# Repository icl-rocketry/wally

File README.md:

# Sirius

Sirius is a two stage rocket being designed and built by ICLR's Altitude Record Team (ART). This repository contains the avionics hardware and software for the rocket.

Sirius has multiple avionics systems on board, with a combination of COTS and SRAD boards used for maximum redundancy and functionality. 

COTS components used:
* [Featherweight Blue Raven](https://www.featherweightaltimeters.com/blue-raven-altimeter.html) flight computer (x2)
* [Featherweight GPS Tracker](https://www.featherweightaltimeters.com/featherweight-gps-tracker.html) (sustainer only)
* [Vodafone Curve](https://eshop.v.vodafone.com/uk/curve-gps-tracker) (booster only)

SRAD boards used:
* Pickle [(developed here)](https://github.com/icl-rocketry/Ricardo-PickleRick)
* WALLY
* Lockie
* PDU

This repository is used for the development of WALLY, Lockie, the PDU and various helper boards. 

## WALLY: Wide Area Landing Location sYstem

Wally complements the COTS trackers and the GPS system onboard Pickle to provide an independent method for trajectory reconstruction and telemetry.

It contains the following elements:
* Microcontroller - ESP32-S3
* GPS - SIM7600G
* LTE - SIM7600G
* RTC - DS3231
* 868MHz LoRa - SX1262
* Barometer - DSP368
* IMU
* Magnetometer
* Storage - Micro SD

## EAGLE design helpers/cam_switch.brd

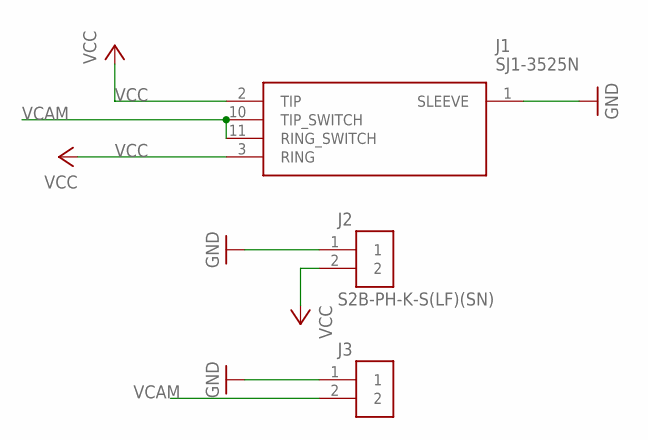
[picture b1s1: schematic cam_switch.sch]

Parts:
J1: SJ1-3525N; SJ13525N
J2, J3: S2B-PH-K-S(LF)(SN)

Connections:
GND: J1.1 (SLEEVE), J2.1, J3.1
VCAM: J1.10 (TIP_SWITCH), J1.11 (RING_SWITCH), J3.2
VCC: J1.2 (TIP), J1.3 (RING), J2.2

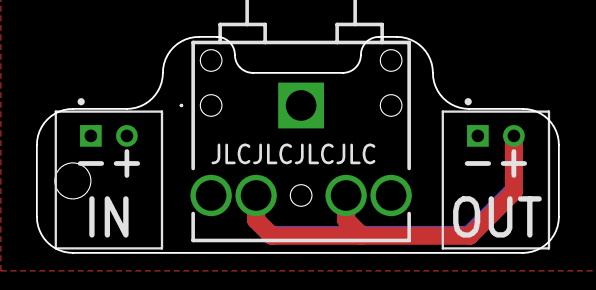
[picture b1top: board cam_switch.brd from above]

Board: 2 copper layers, 29.0 x 12.0 mm, 3 parts (0 on the bottom side), 3 nets.

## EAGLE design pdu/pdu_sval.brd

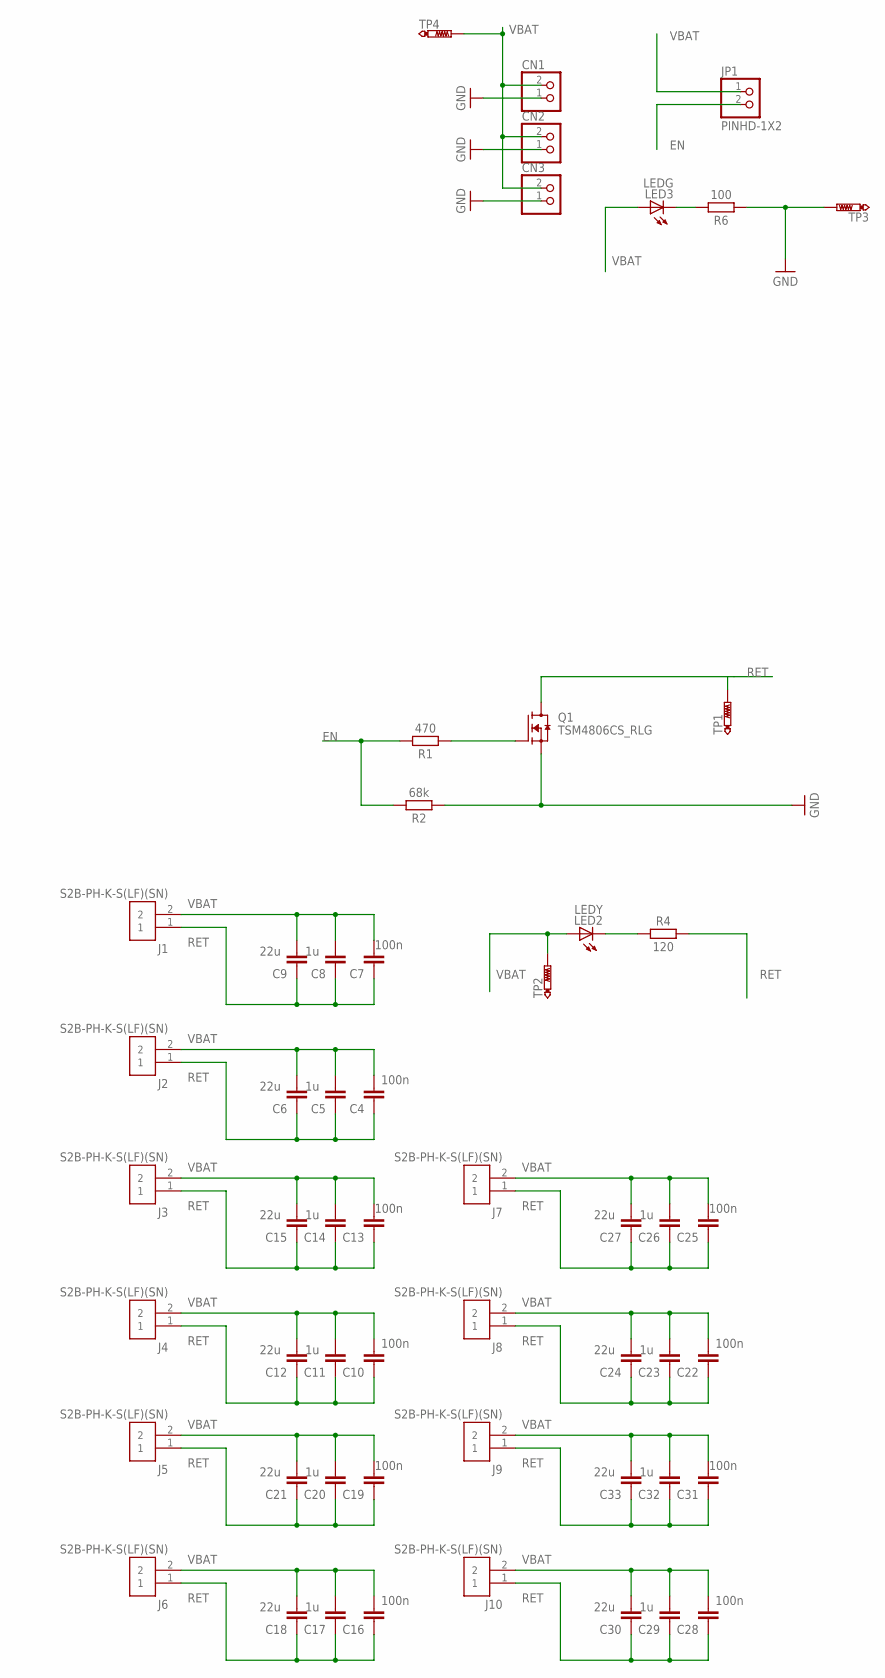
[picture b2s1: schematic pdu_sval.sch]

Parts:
C4, C7, C10, C13, C16, C19, C22, C25, C28, C31: 100n; CAPC1608X85
C5, C8, C11, C14, C17, C20, C23, C26, C29, C32: 1u; CAPC1608X85
C6, C9, C12, C15, C18, C21, C24, C27, C30, C33: 22u; CAPC1608X85
CN1, CN2, CN3: JST_2PIN-THM-RA; JST-PH-2-THM-RA
J1, J2, J3, J4, J5, J6, J7, J8, J9, J10: S2B-PH-K-S(LF)(SN)
JP1: PINHD-1X2; 1X02
LED2: LEDY; CHIPLED_0805
LED3: LEDG; CHIPLED_0805
Q1: TSM4806CS_RLG; SOP127P600X200-8N
R1: 470; RESC1608X60
R2: 68k; RESC1608X60
R4: 120; RESC1608X60
R6: 100; RESC1608X60
TP1, TP2, TP3, TP4: PTR1PAD1-13; P1-13

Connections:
EN: JP1.2, R1.2, R2.2
GND: CN1.1 (2), CN2.1 (2), CN3.1 (2), Q1.1 (S), Q1.2 (S), Q1.3 (S), R2.1, R6.1, TP3.TP
unnamed: Q1.4 (G), R1.1
unnamed: LED3.C, R6.2
unnamed: LED2.C, R4.1
RET: C4.1, C5.1, C6.1, C7.1, C8.1, C9.1, C10.1, C11.1, C12.1, C13.1, C14.1, C15.1, C16.1, C17.1, C18.1, C19.1, C20.1, C21.1, C22.1, C23.1, C24.1, C25.1, C26.1, C27.1, C28.1, C29.1, C30.1, C31.1, C32.1, C33.1, J1.1, J2.1, J3.1, J4.1, J5.1, J6.1, J7.1, J8.1, J9.1, J10.1, Q1.5 (D), Q1.6 (D), Q1.7 (D), Q1.8 (D), R4.2, TP1.TP
VBAT: C4.2, C5.2, C6.2, C7.2, C8.2, C9.2, C10.2, C11.2, C12.2, C13.2, C14.2, C15.2, C16.2, C17.2, C18.2, C19.2, C20.2, C21.2, C22.2, C23.2, C24.2, C25.2, C26.2, C27.2, C28.2, C29.2, C30.2, C31.2, C32.2, C33.2, CN1.2 (1), CN2.2 (1), CN3.2 (1), J1.2, J2.2, J3.2, J4.2, J5.2, J6.2, J7.2, J8.2, J9.2, J10.2, JP1.1, LED2.A, LED3.A, TP2.TP, TP4.TP

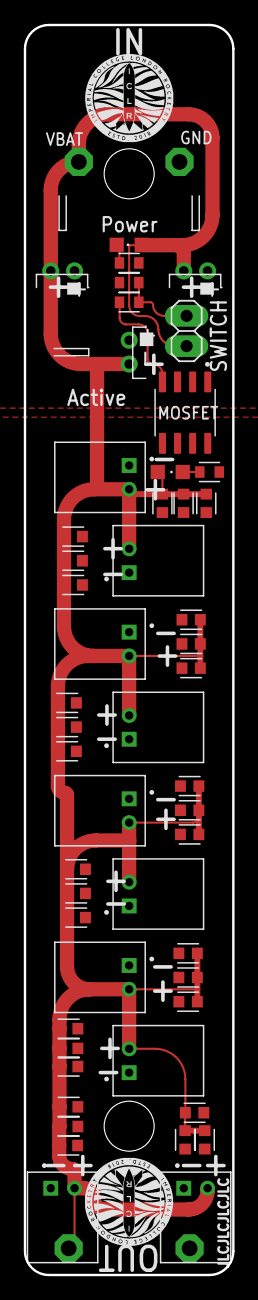
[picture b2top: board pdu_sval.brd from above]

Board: 2 copper layers, 17.5 x 105.0 mm, 55 parts (0 on the bottom side), 7 nets.

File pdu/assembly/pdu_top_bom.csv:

Comment,Designator,Footprint,LCSC Part #
1u,C5 C8 C11 C14 C17 C20 C23 C26 C29 C32,CAPC1608X85,C15849
22u,C6 C9 C12 C15 C18 C21 C24 C27 C30 C33,CAPC1608X85,C59461
68k,R2,RESC1608X60,C23231
100,R6,RESC1608X60,C22775
100n,C4 C7 C10 C13 C16 C19 C22 C25 C28 C31,CAPC1608X85,C14663
120,R4,RESC1608X60,C22787
470,R1,RESC1608X60,C23179
LEDG,LED3,CHIPLED_0805,C2297
LEDY,LED2,CHIPLED_0805,C2296
TSM4806CS_RLG,Q1,SOP127P600X200-8N,

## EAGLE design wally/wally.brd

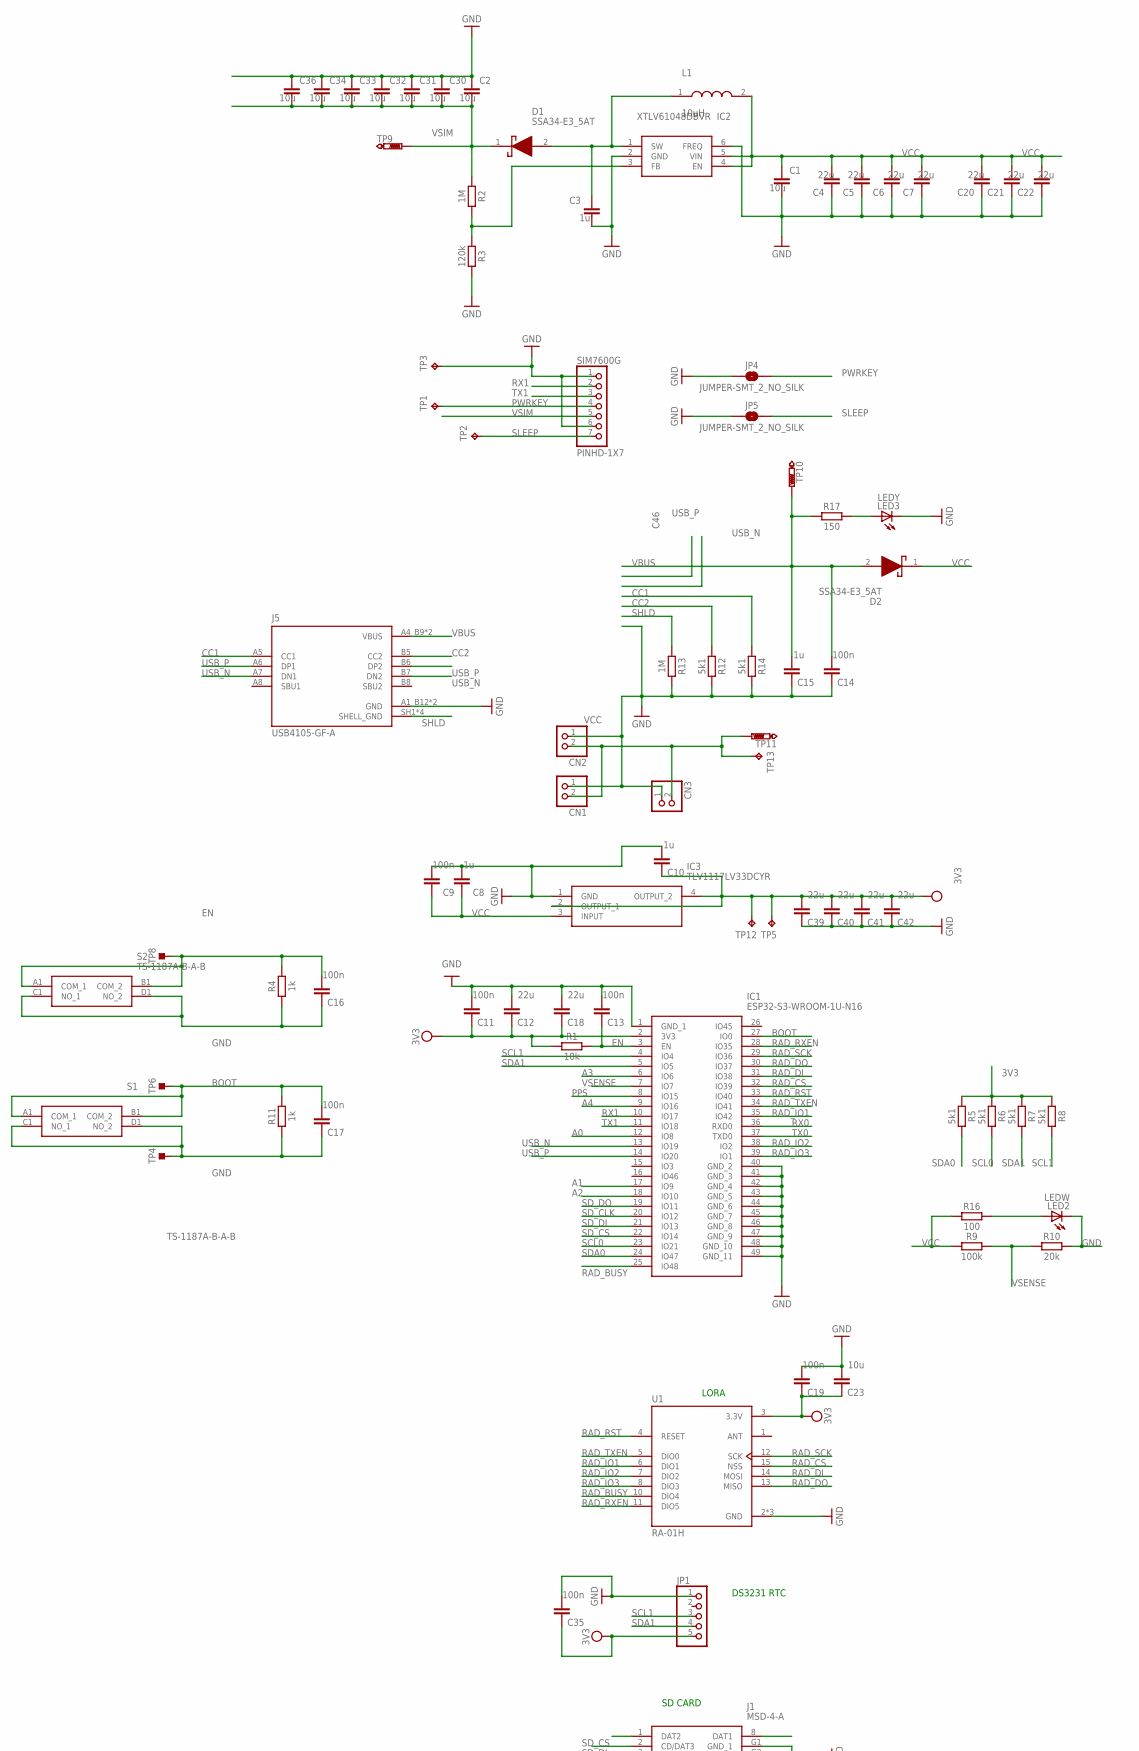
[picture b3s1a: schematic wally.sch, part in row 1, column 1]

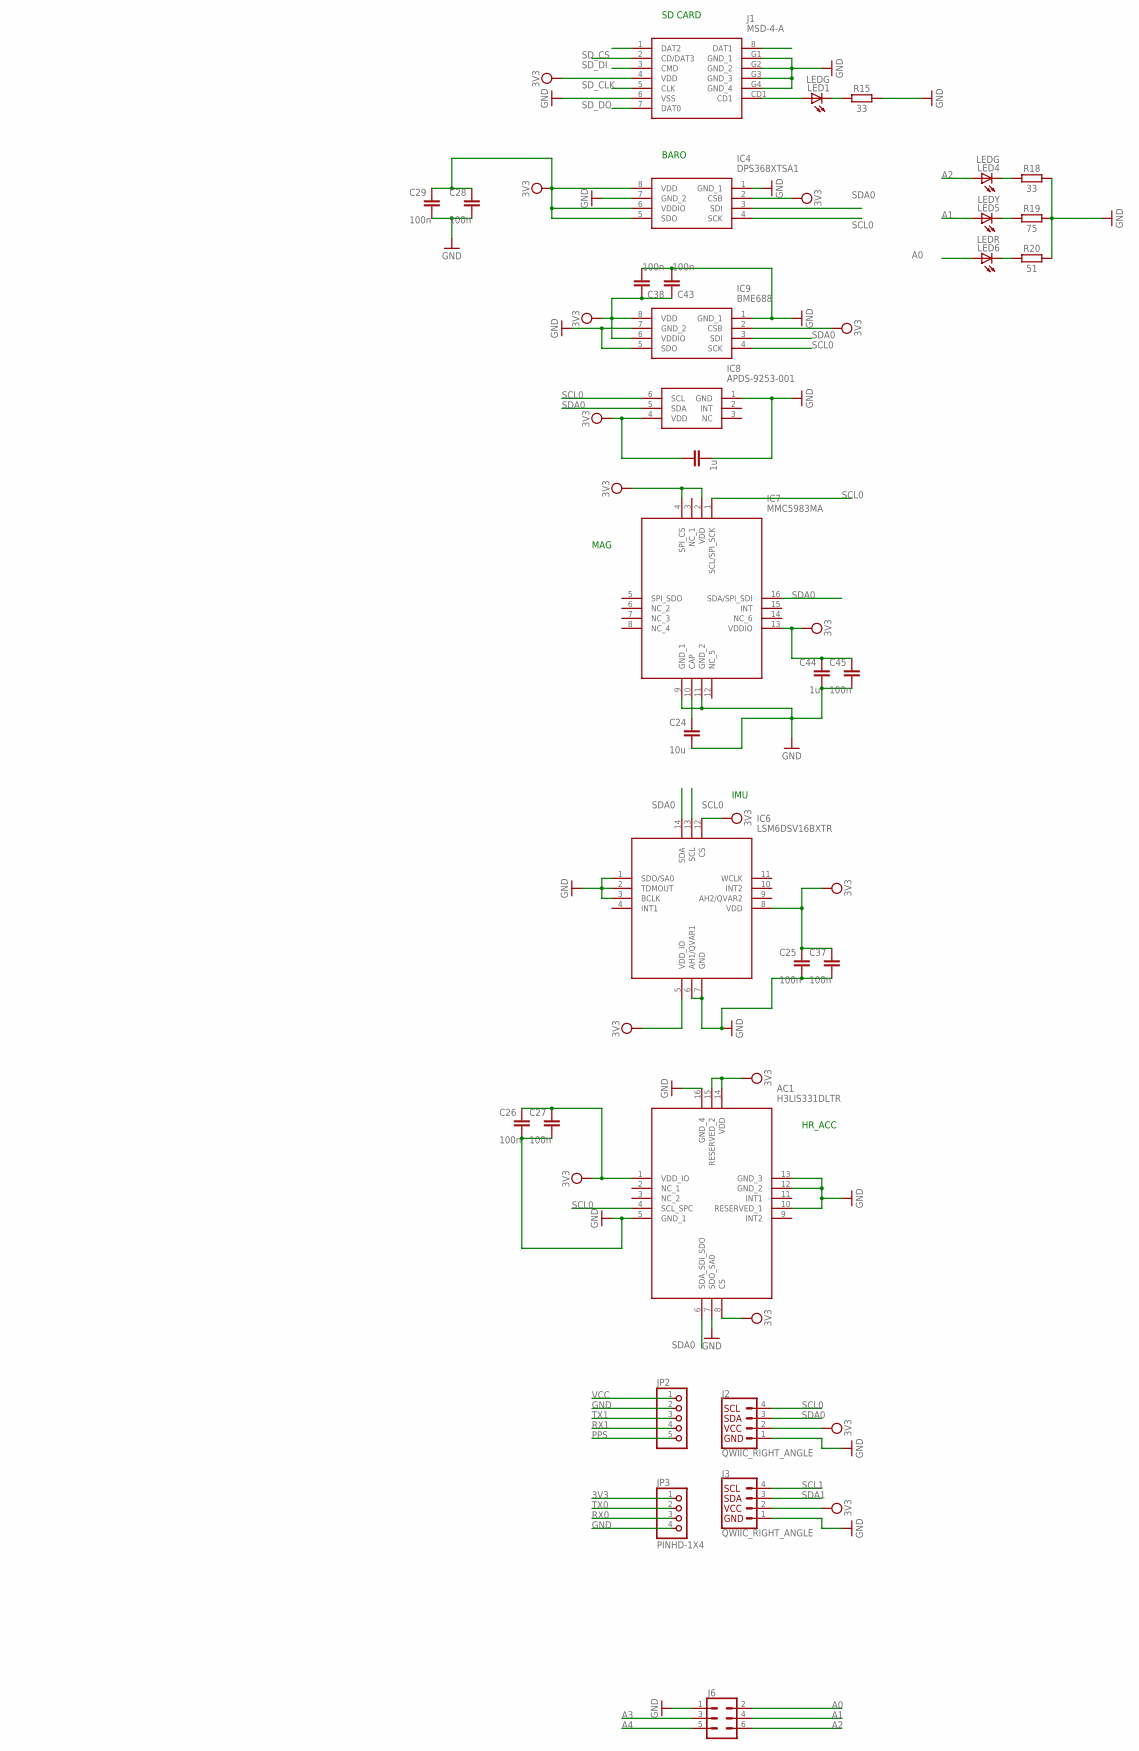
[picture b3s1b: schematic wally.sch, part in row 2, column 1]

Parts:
AC1: H3LIS331DLTR; LIS3DHTR
C1, C23, C24: 10u; CAPC1005X60
C2, C30, C31, C32, C33, C34, C36: 10u; CAPC1608X85
C3, C8, C10, C15, C44, C46: 1u; CAPC1005X60
C4, C5, C6, C7, C12, C18, C20, C21, C22, C39, C40, C41, C42: 22u; CAPC1608X85
C9, C11, C13, C14, C16, C17, C19, C25, C26, C27, C28, C29, C35, C37, C38, C43, C45: 100n; CAPC1005X60
CN1, CN2, CN3: JST_2PIN-THM-RA; JST-PH-2-THM-RA
D1, D2: SSA34-E3_5AT; DIOM5127X229N
IC1: ESP32-S3-WROOM-1U-N16; ESP32S3WROOM1UN16
IC2: XTLV61048DBVR; SOT95P280X145-6N
IC3: TLV1117LV33DCYR; SOT230P700X180-4N
IC4: DPS368XTSA1
IC6: LSM6DSV16BXTR
IC7: MMC5983MA
IC8: APDS-9253-001; APDS9253001
IC9: BME688
J1: MSD-4-A; MSD4A
J2, J3: QWIIC_RIGHT_ANGLE; JST04_1MM_RA
J5: USB4105-GF-A; GCT_USB4105-GF-A
J6: FEMALE 2x3; 2X3-NS
JP1, JP2: PINHD-1X5; 1X05
JP3: PINHD-1X4; 1X04
JP4, JP5: JUMPER-SMT_2_NO_SILK; SMT-JUMPER_2_NO_SILK
L1: 10uH; BMRF00060630100MA1
LED1, LED4: LEDG; CHIPLED_0805
LED2: LEDW; CHIPLED_0805
LED3, LED5: LEDY; CHIPLED_0805
LED6: LEDR; CHIPLED_0805
R1: 10k; RESC1005X40
R2: 1M; RESC1608X60
R3: 120k; RESC1608X60
R4, R11: 1k; RESC1005X40
R5, R6, R7, R8: 5k1; RESC1005X40
R9: 100k; RESC1005X40
R10: 20k; RESC1005X40
R12, R14: 5k1; RESC1608X60
R13: 1M; RESC1005X40
R15, R18: 33; RESC1005X40
R16: 100; RESC1005X40
R17: 150; RESC1608X60
R19: 75; RESC1608X60
R20: 51; RESC1608X60
S1, S2: TS-1187A-B-A-B; TS1187ABAB
SIM7600G: PINHD-1X7; 1X07
TP1, TP2, TP3, TP5, TP12, TP13: TPPAD1-13; P1-13
TP4, TP6, TP8: TESTPOINT_TPS-PAD-036; TESTPOINT_PAD-036
TP9, TP10, TP11: PTR1PAD1-13; P1-13
U1: RA-01H; XCVR_RA-01H

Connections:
3V3: AC1.1 (VDD_IO), AC1.8 (CS), AC1.14 (VDD), AC1.15 (RESERVED_2), C10.1, C11.1, C12.1, C18.1, C19.1, C23.1, C25.1, C26.1, C27.1, C28.1, C29.1, C35.1, C37.1, C38.1, C39.2, C40.2, C41.2, C42.2, C43.1, C44.1, C45.1, C46.1, IC1.2 (3V3), IC3.2 (OUTPUT_1), IC3.4 (OUTPUT_2), IC4.2 (CSB), IC4.5 (SDO), IC4.6 (VDDIO), IC4.8 (VDD), IC6.5 (VDD_IO), IC6.8 (VDD), IC6.12 (CS), IC7.2 (VDD), IC7.4 (SPI_CS), IC7.13 (VDDIO), IC8.4 (VDD), IC9.2 (CSB), IC9.6 (VDDIO), IC9.8 (VDD), J1.4 (VDD), J2.2, J3.2, JP1.5, JP3.1, R1.1, R5.1, R6.1, R7.1, R8.1, TP5.TP, TP12.TP, U1.3 (3.3V)
A0: IC1.12 (IO8), J6.2, LED6.A
A1: IC1.17 (IO9), J6.4, LED5.A
A2: IC1.18 (IO10), J6.6, LED4.A
A3: IC1.6 (IO6), J6.3
A4: IC1.9 (IO16), J6.5
BOOT: C17.2, IC1.27 (IO0), R11.2, S1.A1 (COM_1), S1.B1 (COM_2), TP6.1
CC1: J5.A5 (CC1), R14.1
CC2: J5.B5 (CC2), R12.1
EN: C13.1, C16.2, IC1.3 (EN), R1.2, R4.2, S2.A1 (COM_1), S2.B1 (COM_2), TP8.1
GND: AC1.5 (GND_1), AC1.7 (SDO_SA0), AC1.10 (RESERVED_1), AC1.12 (GND_2), AC1.13 (GND_3), AC1.16 (GND_4), C1.2, C2.1, C3.2, C4.1, C5.1, C6.1, C7.1, C8.2, C9.2, C10.2, C11.2, C12.2, C13.2, C14.1, C15.1, C16.1, C17.1, C18.2, C19.2, C20.1, C21.1, C22.1, C23.2, C24.2, C25.2, C26.2, C27.2, C28.2, C29.2, C30.1, C31.1, C32.1, C33.1, C34.1, C35.2, C36.1, C37.2, C38.2, C39.1, C40.1, C41.1, C42.1, C43.2, C44.2, C45.2, C46.2, CN1.1 (2), CN2.1 (2), CN3.1 (2), IC1.1 (GND_1), IC1.40 (GND_2), IC1.41 (GND_3), IC1.42 (GND_4), IC1.43 (GND_5), IC1.44 (GND_6), IC1.45 (GND_7), IC1.46 (GND_8), IC1.47 (GND_9), IC1.48 (GND_10), IC1.49 (GND_11), IC2.2 (GND), IC2.6 (FREQ), IC3.1 (GND), IC4.1 (GND_1), IC4.7 (GND_2), IC6.1 (SDO/SA0), IC6.2 (TDMOUT), IC6.3 (BCLK), IC6.6 (AH1/QVAR1), IC6.7 (GND), IC7.9 (GND_1), IC7.11 (GND_2), IC8.1 (GND), IC9.1 (GND_1), IC9.5 (SDO), IC9.7 (GND_2), J1.6 (VSS), J1.G1 (GND_1), J1.G2 (GND_2), J1.G3 (GND_3), J1.G4 (GND_4), J2.1, J3.1, J5.A1_B12 (GND), J5.B1_A12 (GND), J6.1, JP1.1, JP2.2, JP3.4, JP4.1, JP5.1, LED2.C, LED3.C, R3.2, R4.1, R10.2, R11.1, R12.2, R13.2, R14.2, R15.2, R18.2, R19.2, R20.2, S1.C1 (NO_1), S1.D1 (NO_2), S2.C1 (NO_1), S2.D1 (NO_2), SIM7600G.1, SIM7600G.6, TP3.TP, TP4.1, U1.2 (GND), U1.9 (GND), U1.16 (GND)
unnamed: LED1.C, R15.1
unnamed: C3.1, D1.2 (A), IC2.1 (SW), L1.1
unnamed: IC2.3 (FB), R2.2, R3.1
unnamed: LED3.A, R17.2
unnamed: C24.1, IC7.10 (CAP)
unnamed: LED4.C, R18.1
unnamed: LED5.C, R19.1
unnamed: LED2.A, R16.2
unnamed: LED6.C, R20.1
unnamed: J1.CD1, LED1.A
PPS: IC1.8 (IO15), JP2.5
PWRKEY: JP4.2, SIM7600G.4, TP1.TP
RAD_BUSY: IC1.25 (IO48), U1.10 (DIO4)
RAD_CS: IC1.32 (IO39), U1.15 (NSS)
RAD_DI: IC1.31 (IO38), U1.14 (MOSI)
RAD_DO: IC1.30 (IO37), U1.13 (MISO)
RAD_IO1: IC1.35 (IO42), U1.6 (DIO1)
RAD_IO2: IC1.38 (IO2), U1.7 (DIO2)
RAD_IO3: IC1.39 (IO1), U1.8 (DIO3)
RAD_RST: IC1.33 (IO40), U1.4 (RESET)
RAD_RXEN: IC1.28 (IO35), U1.11 (DIO5)
RAD_SCK: IC1.29 (IO36), U1.12 (SCK)
RAD_TXEN: IC1.34 (IO41), U1.5 (DIO0)
RX0: IC1.36 (RXD0), JP3.3
RX1: IC1.10 (IO17), JP2.4, SIM7600G.2
SCL0: AC1.4 (SCL_SPC), IC1.23 (IO21), IC4.4 (SCK), IC6.13 (SCL), IC7.1 (SCL/SPI_SCK), IC8.6 (SCL), IC9.4 (SCK), J2.4, R6.2
SCL1: IC1.4 (IO4), J3.4, JP1.3, R8.2
SDA0: AC1.6 (SDA_SDI_SDO), IC1.24 (IO47), IC4.3 (SDI), IC6.14 (SDA), IC7.16 (SDA/SPI_SDI), IC8.5 (SDA), IC9.3 (SDI), J2.3, R5.2
SDA1: IC1.5 (IO5), J3.3, JP1.4, R7.2
SD_CLK: IC1.20 (IO12), J1.5 (CLK)
SD_CS: IC1.22 (IO14), J1.2 (CD/DAT3)
SD_DI: IC1.21 (IO13), J1.3 (CMD)
SD_DO: IC1.19 (IO11), J1.7 (DAT0)
SHLD: J5.SH1 (SHELL_GND), J5.SH2 (SHELL_GND), J5.SH3 (SHELL_GND), J5.SH4 (SHELL_GND), R13.1
SLEEP: JP5.2, SIM7600G.7, TP2.TP
TX0: IC1.37 (TXD0), JP3.2
TX1: IC1.11 (IO18), JP2.3, SIM7600G.3
USB_N: IC1.13 (IO19), J5.A7 (DN1), J5.B7 (DN2)
USB_P: IC1.14 (IO20), J5.A6 (DP1), J5.B6 (DP2)
VBUS: C14.2, C15.2, D2.2 (A), J5.A4_B9 (VBUS), J5.B4_A9 (VBUS), R17.1, TP10.TP
VCC: C1.1, C4.2, C5.2, C6.2, C7.2, C8.1, C9.1, C20.2, C21.2, C22.2, CN1.2 (1), CN2.2 (1), CN3.2 (1), D2.1 (K), IC2.4 (EN), IC2.5 (VIN), IC3.3 (INPUT), JP2.1, L1.2, R9.1, R16.1, TP11.TP, TP13.TP
VSENSE: IC1.7 (IO7), R9.2, R10.1
VSIM: C2.2, C30.2, C31.2, C32.2, C33.2, C34.2, C36.2, D1.1 (K), R2.1, SIM7600G.5, TP9.TP

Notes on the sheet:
DS3231 RTC
LORA
SD CARD
BARO
IMU
HR_ACC
MAG

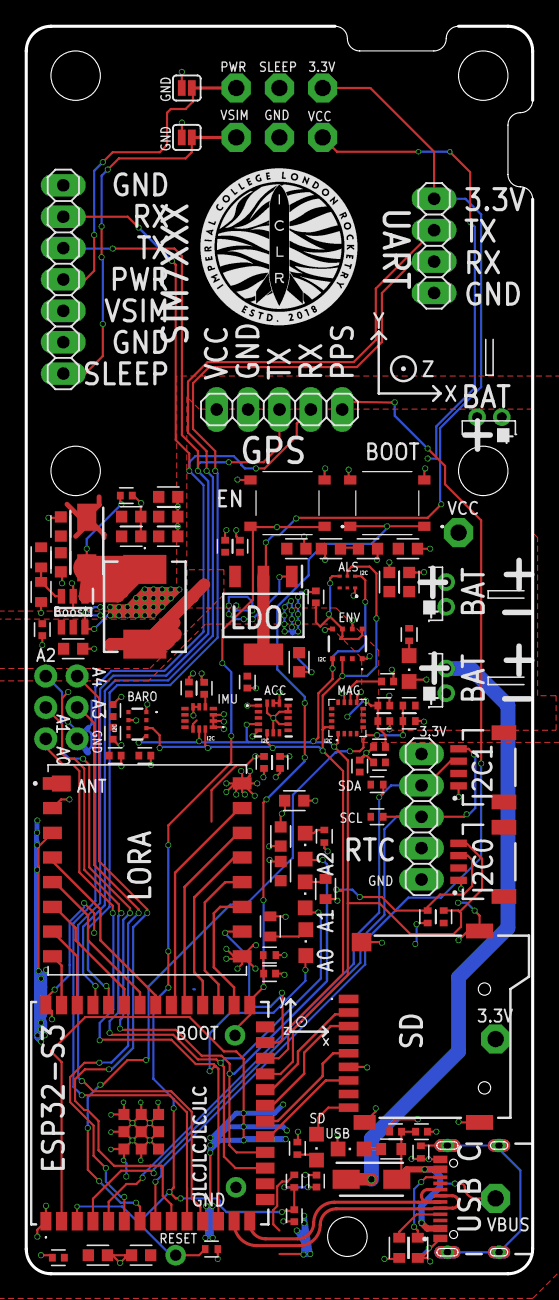
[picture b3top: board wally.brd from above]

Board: 2 copper layers, 41.0 x 101.0 mm, 113 parts (0 on the bottom side), 54 nets.

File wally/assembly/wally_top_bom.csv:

Comment,Designator,Footprint,LCSC Part #
1M,R2,RESC1608X60,C22935
1M,R13,RESC1005X40,C26083
1k,R4 R11,RESC1005X40,C11702
1u,C3 C8 C10 C15 C44 C46,CAPC1005X60,C52923
5k1,R5 R6 R7 R8,RESC1005X40,C25905
5k1,R12 R14,RESC1608X60,C23186
10k,R1,RESC1005X40,C25744
10u,C1,CAPC1005X60,C15525
10u,C2,CAPC1608X85,C96446
10u,C23 C24,CAPC1005X60,C15525
10u,C30 C31 C32 C33 C34 C36,CAPC1608X85,C96446
10uH,L1,BMRF00060630100MA1,
20k,R10,RESC1005X40,C25765
22u,C4 C5 C6 C7 C12 C18 C20 C21 C22 C39 C40 C41 C42,CAPC1608X85,C59461
33,R15 R18,RESC1005X40,C25105
51,R20,RESC1608X60,C23197
75,R19,RESC1608X60,C4275
100,R16,RESC1005X40,C25076
100k,R9,RESC1005X40,C25741
100n,C9 C11 C13 C14 C16 C17 C19 C25 C26 C27 C28 C29 C35 C37 C38 C43 C45,CAPC1005X60,C1525
120k,R3,RESC1608X60,C25808
150,R17,RESC1608X60,C22808
APDS-9253-001,IC8,APDS9253001,
BME688,IC9,BME688,
DPS368XTSA1,IC4,DPS368XTSA1,
ESP32-S3-WROOM-1U-N16,IC1,ESP32S3WROOM1UN16,
H3LIS331DLTR,AC1,LIS3DHTR,
JUMPER-SMT_2_NO_SILK,JP4 JP5,SMT-JUMPER_2_NO_SILK,
LEDG,LED1 LED4,CHIPLED_0805,C2297
LEDR,LED6,CHIPLED_0805,C84256
LEDW,LED2,CHIPLED_0805,C34499
LEDY,LED3 LED5,CHIPLED_0805,C2296
LSM6DSV16BXTR,IC6,LSM6DSV16BXTR,
MMC5983MA,IC7,MMC5983MA,
MSD-4-A,J1,MSD4A,
QWIIC_RIGHT_ANGLE,J2 J3,JST04_1MM_RA,
RA-01H,U1,XCVR_RA-01H,
SSA34-E3_5AT,D1 D2,DIOM5127X229N,C22452
TLV1117LV33DCYR,IC3,SOT230P700X180-4N,C15578
TS-1187A-B-A-B,S1 S2,TS1187ABAB,C318884
USB4105-GF-A,J5,GCT_USB4105-GF-A,C3039324
XTLV61048DBVR,IC2,SOT95P280X145-6N,C2861467

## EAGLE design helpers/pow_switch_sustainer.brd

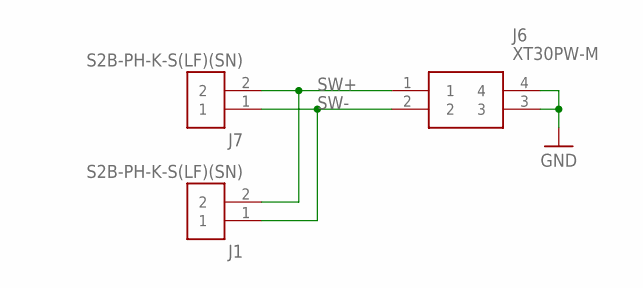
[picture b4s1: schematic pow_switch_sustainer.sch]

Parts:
J1, J7: S2B-PH-K-S(LF)(SN)
J6: XT30PW-M; XT30PWM

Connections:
GND: J6.3, J6.4
SW+: J1.2, J6.1, J7.2
SW-: J1.1, J6.2, J7.1

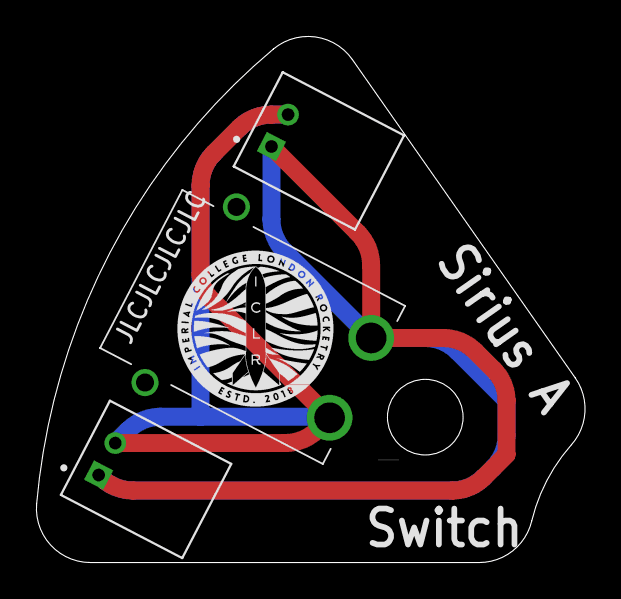
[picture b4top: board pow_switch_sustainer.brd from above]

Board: 2 copper layers, 30.5 x 29.2 mm, 3 parts (0 on the bottom side), 3 nets.

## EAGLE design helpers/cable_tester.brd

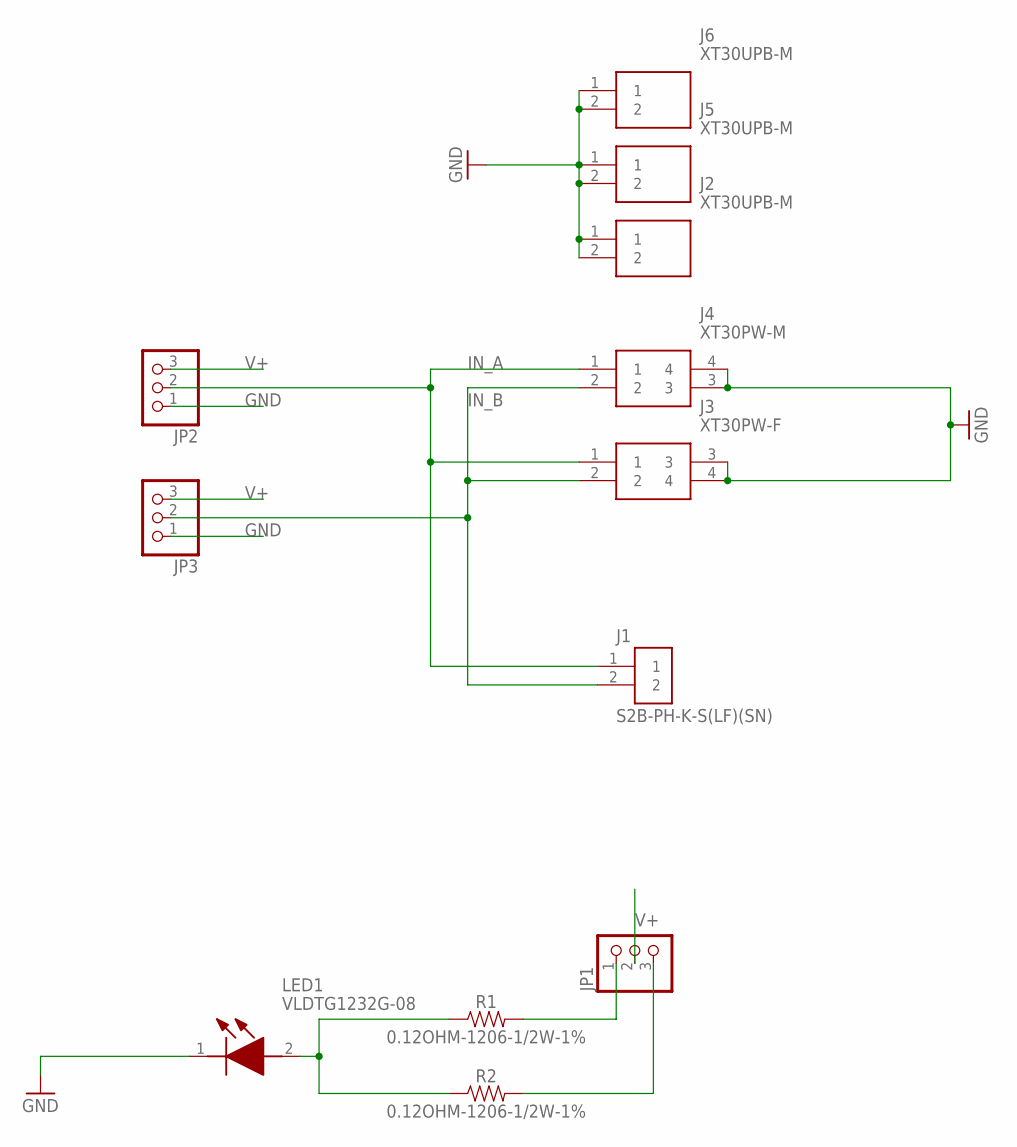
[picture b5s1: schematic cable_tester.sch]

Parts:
J1: S2B-PH-K-S(LF)(SN)
J2, J5, J6: XT30UPB-M; SHDR2W160P0X500_1X2_1020X520X1
J3: XT30PW-F; XT30PWF
J4: XT30PW-M; XT30PWM
JP1, JP2, JP3: PINHD-1X3; 1X03
LED1: VLDTG1232G-08; VLDTG1232G08
R1, R2: 0.12OHM-1206-1/2W-1%; 1206

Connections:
GND: J2.1, J2.2, J3.3, J3.4, J4.3, J4.4, J5.1, J5.2, J6.1, J6.2, JP2.1, JP3.1, LED1.1 (K)
IN_A: J1.1, J3.1, J4.1, JP2.2
IN_B: J1.2, J3.2, J4.2, JP3.2
unnamed: LED1.2 (A), R1.1, R2.1
unnamed: JP1.1, R1.2
unnamed: JP1.3, R2.2
V+: JP1.2, JP2.3, JP3.3

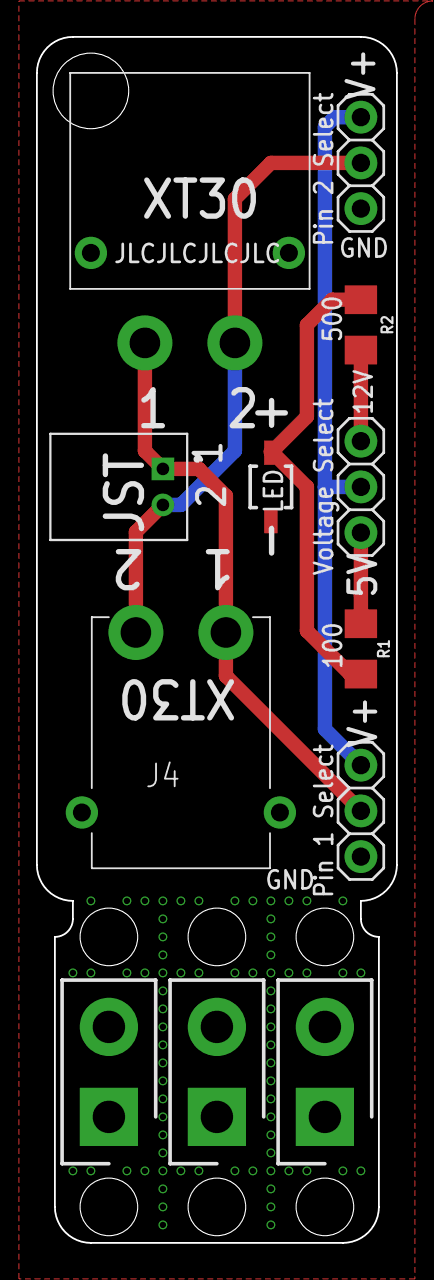
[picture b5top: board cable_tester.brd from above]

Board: 2 copper layers, 20.0 x 67.0 mm, 12 parts (0 on the bottom side), 7 nets.

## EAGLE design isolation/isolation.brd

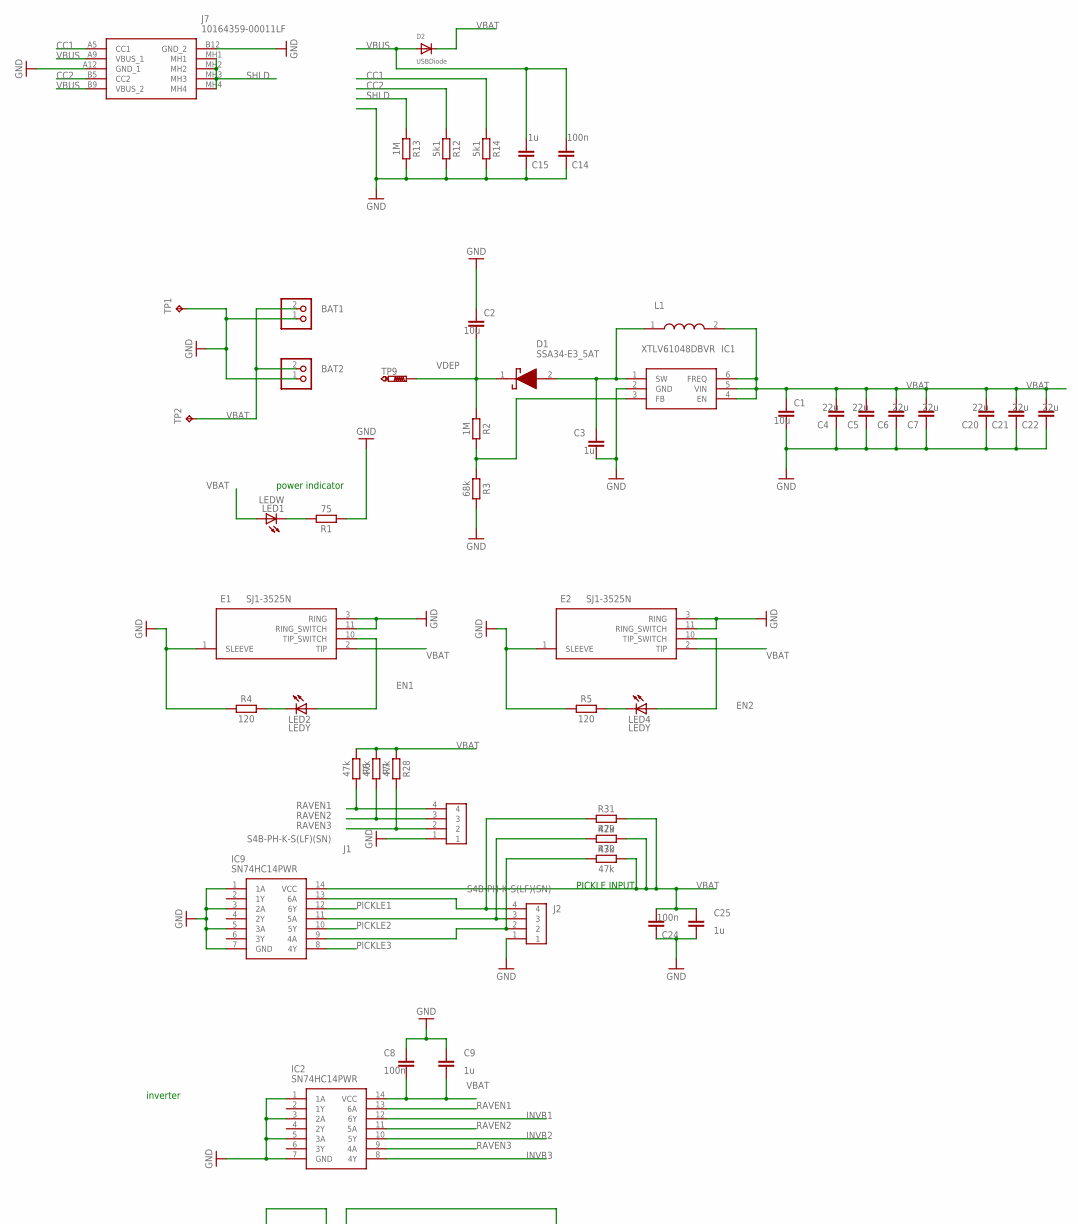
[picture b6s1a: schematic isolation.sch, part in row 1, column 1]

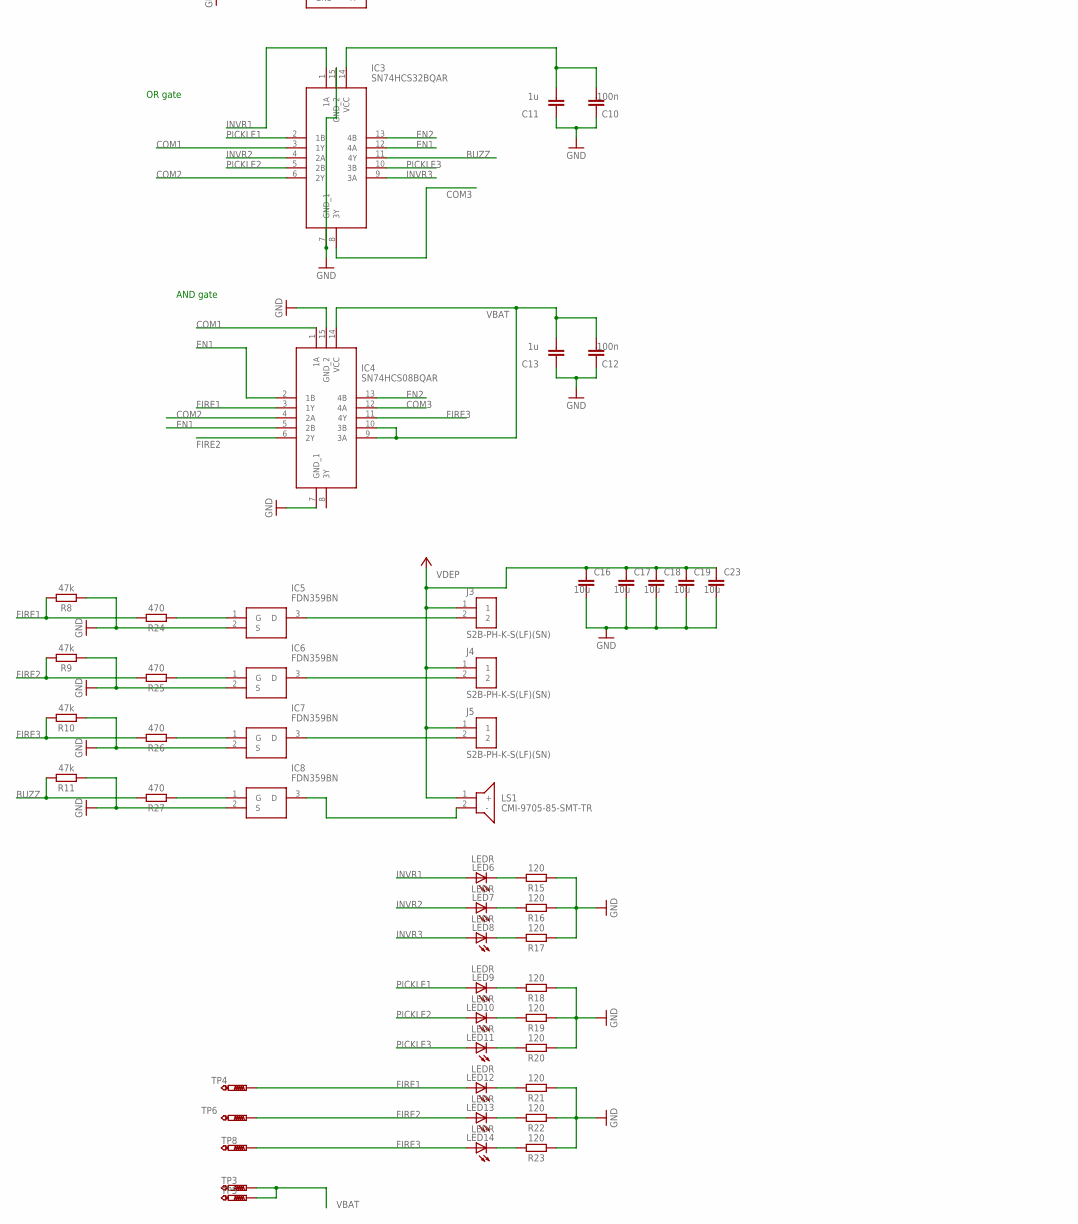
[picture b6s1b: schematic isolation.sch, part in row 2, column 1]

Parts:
BAT1, BAT2: JST_2PIN-THM-RA; JST-PH-2-THM-RA
C1: 10u; CAPC1005X60
C2, C16, C17, C18, C19, C23: 10u; CAPC1608X85
C3, C9, C11, C13, C15, C25: 1u; CAPC1005X60
C4, C5, C6, C7, C20, C21, C22: 22u; CAPC1608X85
C8, C10, C12, C14, C24: 100n; CAPC1005X60
D1: SSA34-E3_5AT; DIOM5127X229N
D2: USBDiode; SOD-123FL
E1, E2: SJ1-3525N; SJ13525N
IC1: XTLV61048DBVR; SOT95P280X145-6N
IC2, IC9: SN74HC14PWR; SOP65P640X120-14N
IC3: SN74HCS32BQAR
IC4: SN74HCS08BQAR
IC5, IC6, IC7, IC8: FDN359BN; SOT95P251X112-3N
J1, J2: S4B-PH-K-S(LF)(SN)
J3, J4, J5: S2B-PH-K-S(LF)(SN)
J7: 10164359-00011LF; 1016435900011LF
L1: 10μH; BMRF00060630100MA1
LED1: LEDW; CHIPLED_0805
LED2, LED4: LEDY; CHIPLED_0805
LED6, LED7, LED8, LED9, LED10, LED11, LED12, LED13, LED14: LEDR; CHIPLED_0805
LS1: CMI-9705-85-SMT-TR; CMI970585SMTTR
R1: 75; RESC1608X60
R2, R13: 1M; RESC1005X40
R3: 68k; RESC1608X60
R4, R5, R15, R16, R17, R18, R19, R20, R21, R22, R23: 120; RESC1005X40
R6, R7, R8, R9, R10, R11, R28, R29, R30, R31: 47k; RESC1005X40
R12, R14: 5k1; RESC1005X40
R24, R25, R26, R27: 470; RESC1005X40
TP1: TPPAD1-13; P1-13
TP2: TPPAD1-17; P1-17
TP3, TP4, TP5, TP6, TP8, TP9: PTR1PAD1-13; P1-13

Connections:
BUZZ: IC3.11 (4Y), R11.2, R27.2
CC1: J7.A5 (CC1), R14.1
CC2: J7.B5 (CC2), R12.1
COM1: IC3.3 (1Y), IC4.1 (1A)
COM2: IC3.6 (2Y), IC4.4 (2A)
COM3: IC3.8 (3Y), IC4.12 (4A)
EN1: E1.10 (TIP_SWITCH), IC3.12 (4A), IC4.2 (1B), IC4.5 (2B), LED2.A
EN2: E2.10 (TIP_SWITCH), IC3.13 (4B), IC4.13 (4B), LED4.A
FIRE1: IC4.3 (1Y), LED12.A, R8.2, R24.2, TP4.TP
FIRE2: IC4.6 (2Y), LED13.A, R9.2, R25.2, TP6.TP
FIRE3: IC4.11 (4Y), LED14.A, R10.2, R26.2, TP8.TP
GND: BAT1.1 (2), BAT2.1 (2), C1.2, C2.1, C3.2, C4.1, C5.1, C6.1, C7.1, C8.1, C9.1, C10.1, C11.1, C12.1, C13.1, C14.1, C15.1, C16.2, C17.2, C18.2, C19.2, C20.1, C21.1, C22.1, C23.2, C24.1, C25.2, E1.1 (SLEEVE), E1.3 (RING), E1.11 (RING_SWITCH), E2.1 (SLEEVE), E2.3 (RING), E2.11 (RING_SWITCH), IC1.2 (GND), IC2.1 (1A), IC2.3 (2A), IC2.5 (3A), IC2.7 (GND), IC3.7 (GND_1), IC3.15 (GND_2), IC4.7 (GND_1), IC4.15 (GND_2), IC5.2 (S), IC6.2 (S), IC7.2 (S), IC8.2 (S), IC9.1 (1A), IC9.3 (2A), IC9.5 (3A), IC9.7 (GND), J1.1, J2.1, J7.A12 (GND_1), J7.B12 (GND_2), R1.1, R3.2, R4.1, R5.1, R8.1, R9.1, R10.1, R11.1, R12.2, R13.2, R14.2, R15.1, R16.1, R17.1, R18.1, R19.1, R20.1, R21.1, R22.1, R23.1, TP1.TP
INVR1: IC2.12 (6Y), IC3.1 (1A), LED6.A
INVR2: IC2.10 (5Y), IC3.4 (2A), LED7.A
INVR3: IC2.8 (4Y), IC3.9 (3A), LED8.A
unnamed: LED1.C, R1.2
unnamed: C3.1, D1.2 (A), IC1.1 (SW), L1.1
unnamed: IC1.3 (FB), R2.2, R3.1
unnamed: LED4.C, R5.2
unnamed: LED2.C, R4.2
unnamed: LED9.C, R18.2
unnamed: LED10.C, R19.2
unnamed: LED11.C, R20.2
unnamed: LED12.C, R21.2
unnamed: LED13.C, R22.2
unnamed: LED14.C, R23.2
unnamed: IC7.3 (D), J5.2
unnamed: IC6.3 (D), J4.2
unnamed: IC9.13 (6A), J2.4, R31.1
unnamed: IC5.3 (D), J3.2
unnamed: LED7.C, R16.2
unnamed: IC9.11 (5A), J2.3, R29.1
unnamed: IC5.1 (G), R24.1
unnamed: IC6.1 (G), R25.1
unnamed: IC8.3 (D), LS1.2 (-)
unnamed: LED8.C, R17.2
unnamed: IC7.1 (G), R26.1
unnamed: IC8.1 (G), R27.1
unnamed: IC9.9 (4A), J2.2, R30.1
unnamed: LED6.C, R15.2
PICKLE1: IC3.2 (1B), IC9.12 (6Y), LED9.A
PICKLE2: IC3.5 (2B), IC9.10 (5Y), LED10.A
PICKLE3: IC3.10 (3B), IC9.8 (4Y), LED11.A
RAVEN1: IC2.13 (6A), J1.4, R6.2
RAVEN2: IC2.11 (5A), J1.3, R7.2
RAVEN3: IC2.9 (4A), J1.2, R28.2
SHLD: J7.MH1, J7.MH2, J7.MH3, J7.MH4, R13.1
VBAT: BAT1.2 (1), BAT2.2 (1), C1.1, C4.2, C5.2, C6.2, C7.2, C8.2, C9.2, C10.2, C11.2, C12.2, C13.2, C20.2, C21.2, C22.2, C24.2, C25.1, D2.C, E1.2 (TIP), E2.2 (TIP), IC1.4 (EN), IC1.5 (VIN), IC1.6 (FREQ), IC2.14 (VCC), IC3.14 (VCC), IC4.9 (3A), IC4.10 (3B), IC4.14 (VCC), IC9.14 (VCC), L1.2, LED1.A, R6.1, R7.1, R28.1, R29.2, R30.2, R31.2, TP2.TP, TP3.TP, TP5.TP
VBUS: C14.2, C15.2, D2.A, J7.A9 (VBUS_1), J7.B9 (VBUS_2)
VDEP: C2.2, C16.1, C17.1, C18.1, C19.1, C23.1, D1.1 (K), J3.1, J4.1, J5.1, LS1.1 (+), R2.1, TP9.TP

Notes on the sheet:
power indicator
inverter
OR gate
AND gate
PICKLE INPUT

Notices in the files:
parts and their libraries:
SparkFun-Resistors: Licensing: Creative Commons ShareAlike 4.0 International - https://creativecommons.org/licenses/by-sa/4.0
